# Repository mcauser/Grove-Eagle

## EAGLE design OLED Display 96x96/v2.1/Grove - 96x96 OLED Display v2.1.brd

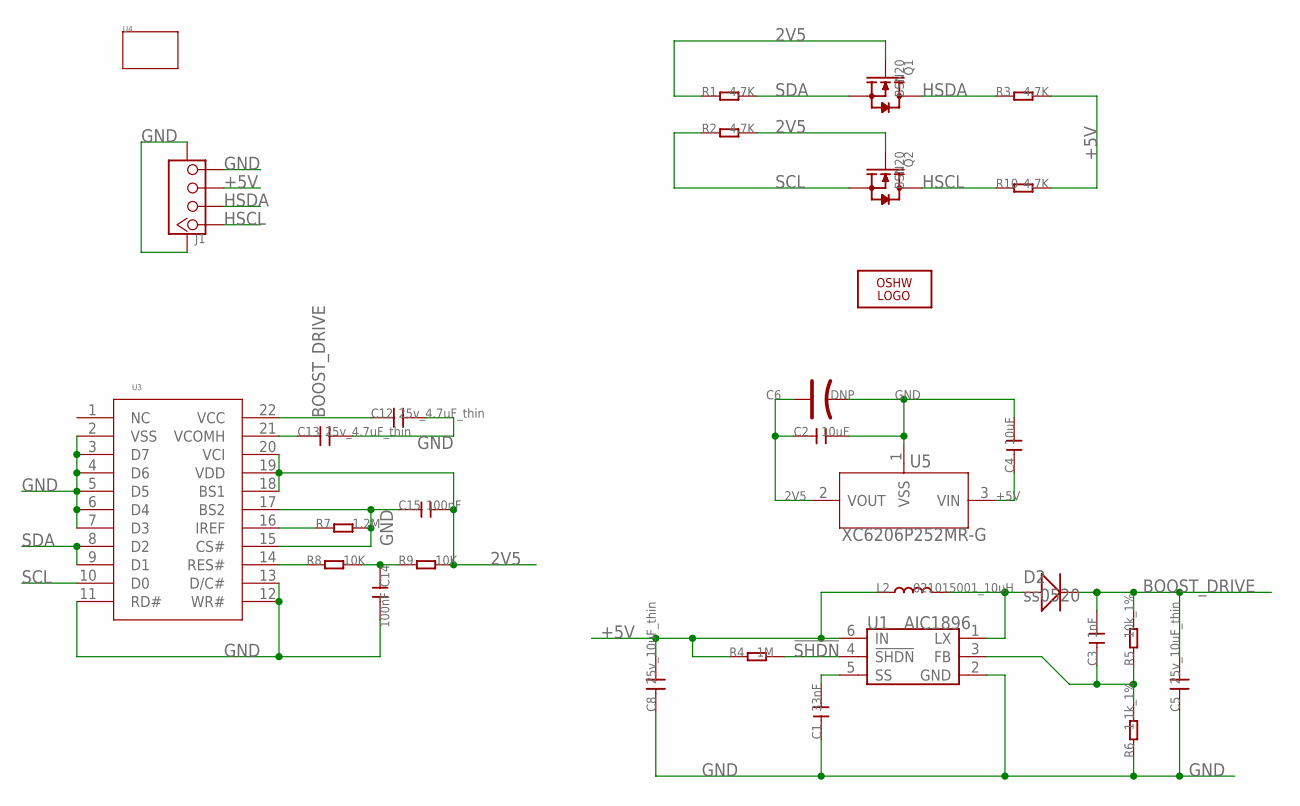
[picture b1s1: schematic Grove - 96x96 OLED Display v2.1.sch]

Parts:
C1: 33nF; C0603
C2, C4: 10uF; C0805
C3: 1nF; C0603
C5, C8: 25v_10uF_thin; 0805
C6: DNP; AVX-A
C12, C13: 25v_4.7uF_thin; 0805
C14, C15: 100nF; C0603
D2: ss0520; SOD123
J1: TWIG-4P-2.0-SMD-FEMALE-REINFORCE'90D'; 4P-SMD-2.0-90D
L2: 021015001_10uH; 0806
LOGO2: LOGO-OSHW-FILLX0200-NT; OSHW_FILLX200_NOTEXT
Q1, Q2: BSN20; SOT23
R1, R2, R3, R10: 4.7K; R0603
R4: 1M; R0603
R5: 10k_1%; R0603
R6: 1.1k_1%; R0603
R7: 1.2M; 0603
R8, R9: 10K; 0603
U1: AIC1896; SOT23-6
U3: LY120-096096
U4: TWIG-2X2U; 2X2U-DIM-W/-DRILL
U5: XC6206P252MR-G; SOT23

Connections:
2V5: C2.1, C6.+, C15.2, Q1.1 (G), Q2.1 (G), R1.1, R2.2, R9.2, U3.18 (BS1), U3.19 (VDD), U3.20 (VCI), U5.2 (VOUT)
!SHDN: R4.2, U1.4 (!SHDN)
+5V: C4.1, C8.2, J1.3, L2.1, R3.2, R4.1, R10.2, U1.6 (IN), U5.3 (VIN)
BOOST_DRIVE: C3.2, C5.2, C12.1, D2.-, R5.2, U3.22 (VCC)
GND: C1.1, C2.2, C4.2, C5.1, C6.-, C8.1, C12.2, C13.2, C14.2, C15.1, J1.4, J1.SS1, J1.SS2, R6.1, R7.2, U1.2 (GND), U3.2 (VSS), U3.3 (D7), U3.4 (D6), U3.5 (D5), U3.6 (D4), U3.7 (D3), U3.11 (RD#), U3.12 (WR#), U3.13 (D/C#), U3.15 (CS#), U3.17 (BS2), U5.1 (VSS)
HSCL: J1.1, Q2.3 (D), R10.1
HSDA: J1.2, Q1.3 (D), R3.1
unnamed: D2.+, L2.2, U1.1 (LX)
unnamed: C1.2, U1.5 (SS)
unnamed: C3.1, R5.1, R6.2, U1.3 (FB)
unnamed: C13.1, U3.21 (VCOMH)
unnamed: R7.1, U3.16 (IREF)
unnamed: R8.1, U3.14 (RES#)
unnamed: C14.1, R8.2, R9.1
SCL: Q2.2 (S), R2.1, U3.10 (D0)
SDA: Q1.2 (S), R1.2, U3.8 (D2), U3.9 (D1)

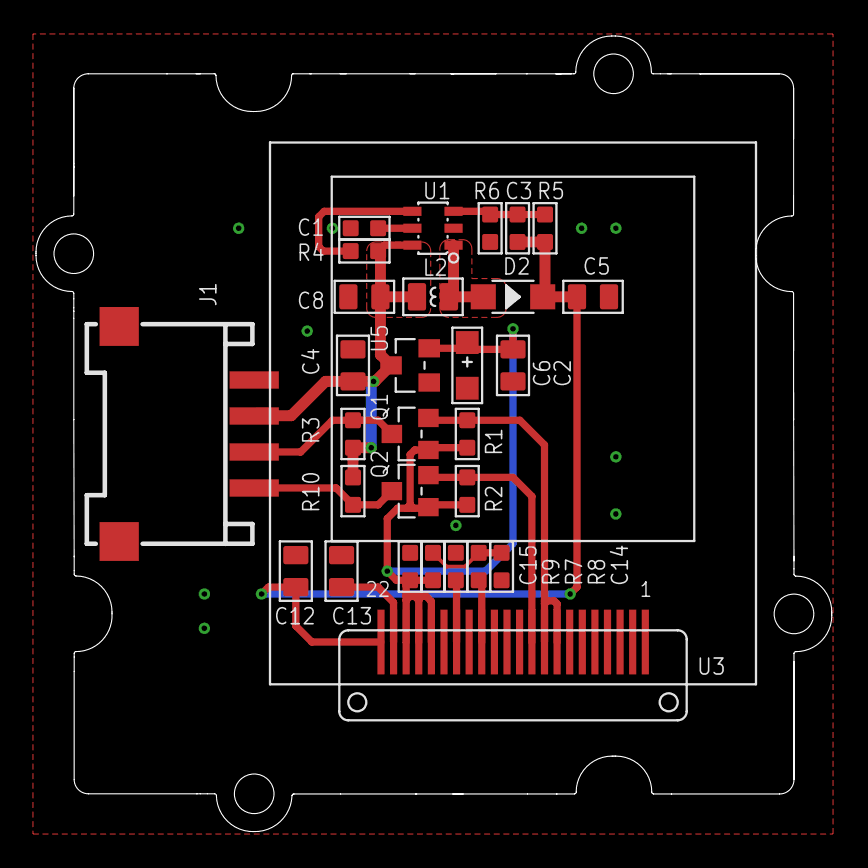
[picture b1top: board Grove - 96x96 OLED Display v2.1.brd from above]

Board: 2 copper layers, 44.2 x 44.2 mm, 32 parts (2 on the bottom side), 16 nets.

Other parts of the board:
U$1: TWIGLOGO

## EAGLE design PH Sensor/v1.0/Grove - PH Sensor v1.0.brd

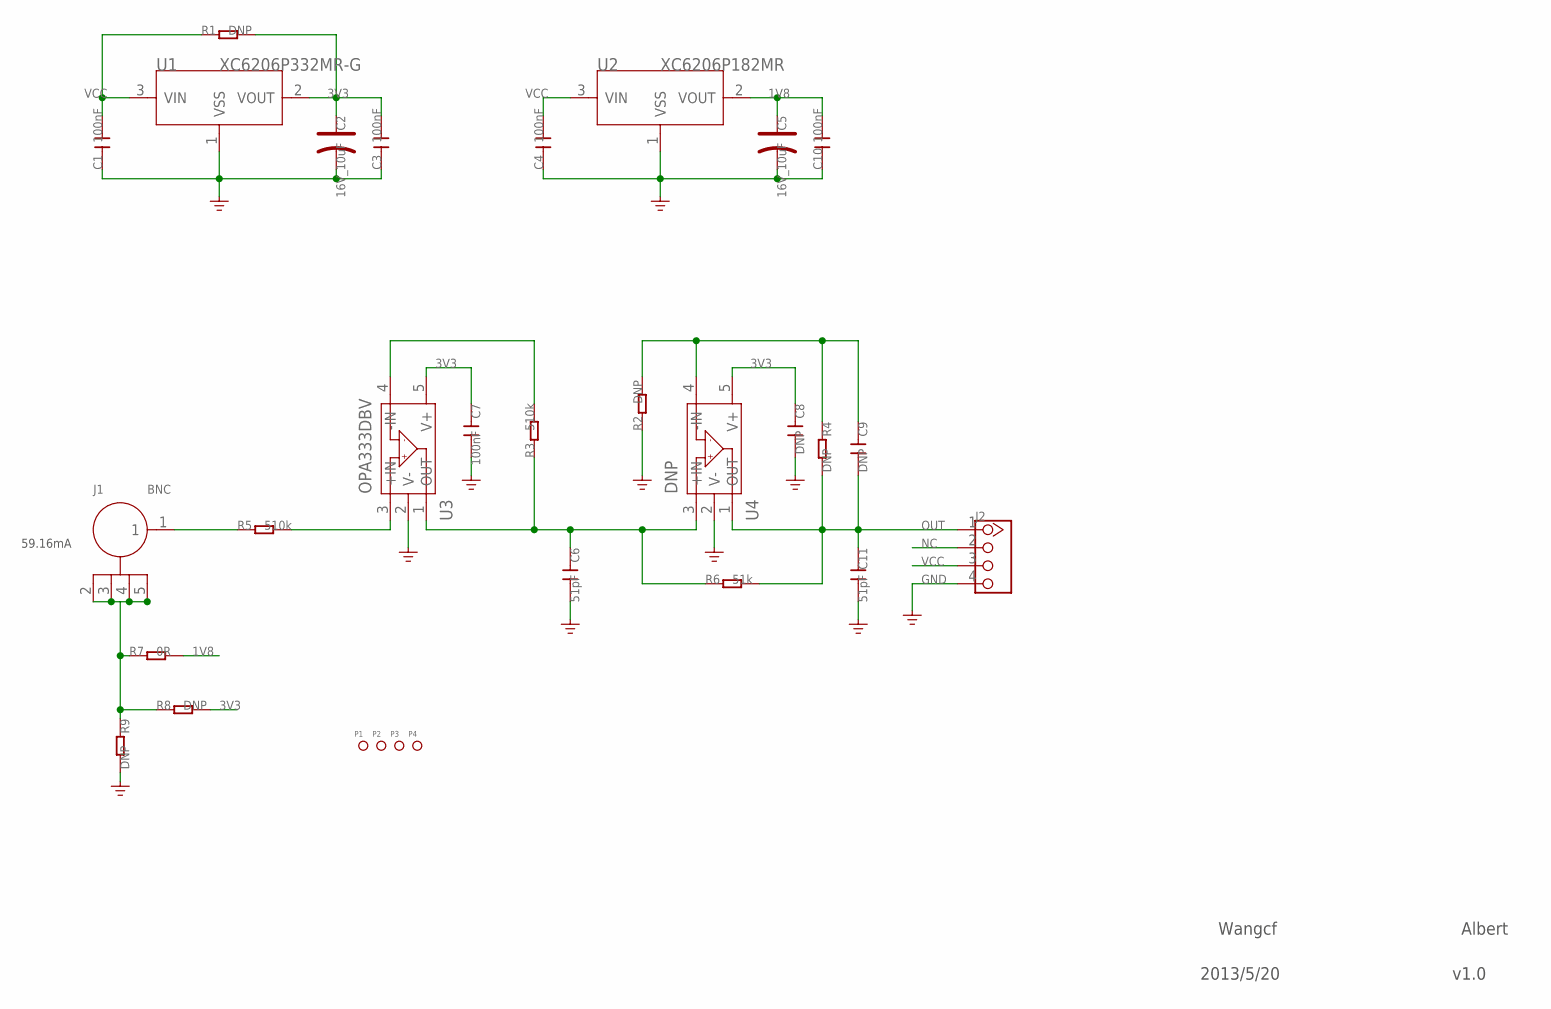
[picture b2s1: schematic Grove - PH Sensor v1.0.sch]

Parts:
C1, C3, C4, C7, C10: 100nF; C0603
C2, C5: 16V_10uF; AVX-A
C6, C11: 51pF; C0603
C8, C9: DNP; C0603
J1: BNC; 2P-10X10X12H-90D
J2: TWIG-4P-2.0-2.0; 4P-2.0
P1, P2, P3, P4: PAD-MARK; ROUND-MARK-1.0
R1, R2, R4, R8, R9: DNP; R0603
R3, R5: 510k; R0603
R6: 51k; R0603
R7: 0R; R0603
U1: XC6206P332MR-G; SOT23
U2: XC6206P182MR; SOT23
U3: OPA333DBV; SOT23-5
U4: DNP; SOT23-5

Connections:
1V8: C5.+, C10.2, R7.2, U2.2 (VOUT)
3V3: C2.+, C3.2, C7.1, C8.1, R1.2, R8.2, U1.2 (VOUT), U3.5 (V+), U4.5 (V+)
GND: C1.1, C2.-, C3.1, C4.1, C5.-, C6.2, C7.2, C8.2, C10.1, C11.2, J2.4, R2.1, R9.2, U1.1 (VSS), U2.1 (VSS), U3.2 (V-), U4.2 (V-)
unnamed: J1.1, R5.1
unnamed: R5.2, U3.3 (+IN)
unnamed: C6.1, R3.1, R6.1, U3.1 (OUT), U4.3 (+IN)
unnamed: R3.2, U3.4 (-IN)
unnamed: C9.1, R2.2, R4.1, U4.4 (-IN)
unnamed: J1.2, J1.3, J1.4, J1.5, R7.1, R8.1, R9.1
NC: J2.2
OUT: C9.2, C11.1, J2.1, R4.2, R6.2, U4.1 (OUT)
VCC: C1.2, C4.2, J2.3, R1.1, U1.3 (VIN), U2.3 (VIN)

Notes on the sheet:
59.16mA
Wangcf
Albert
2013/5/20
v1.0

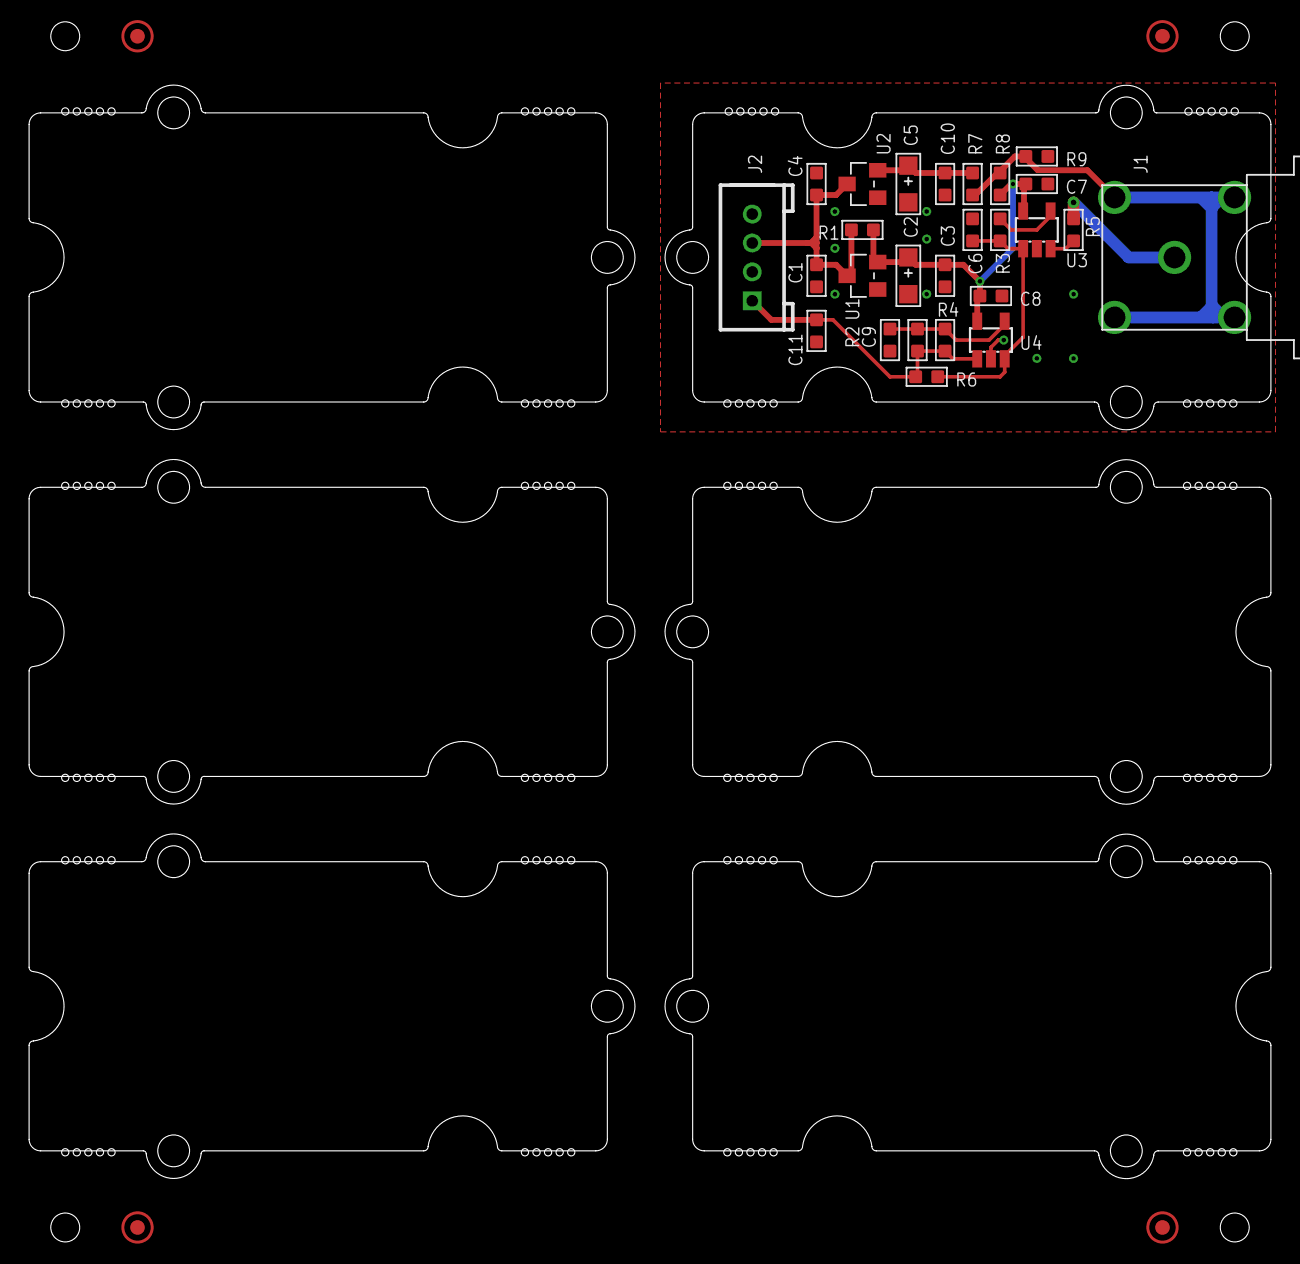
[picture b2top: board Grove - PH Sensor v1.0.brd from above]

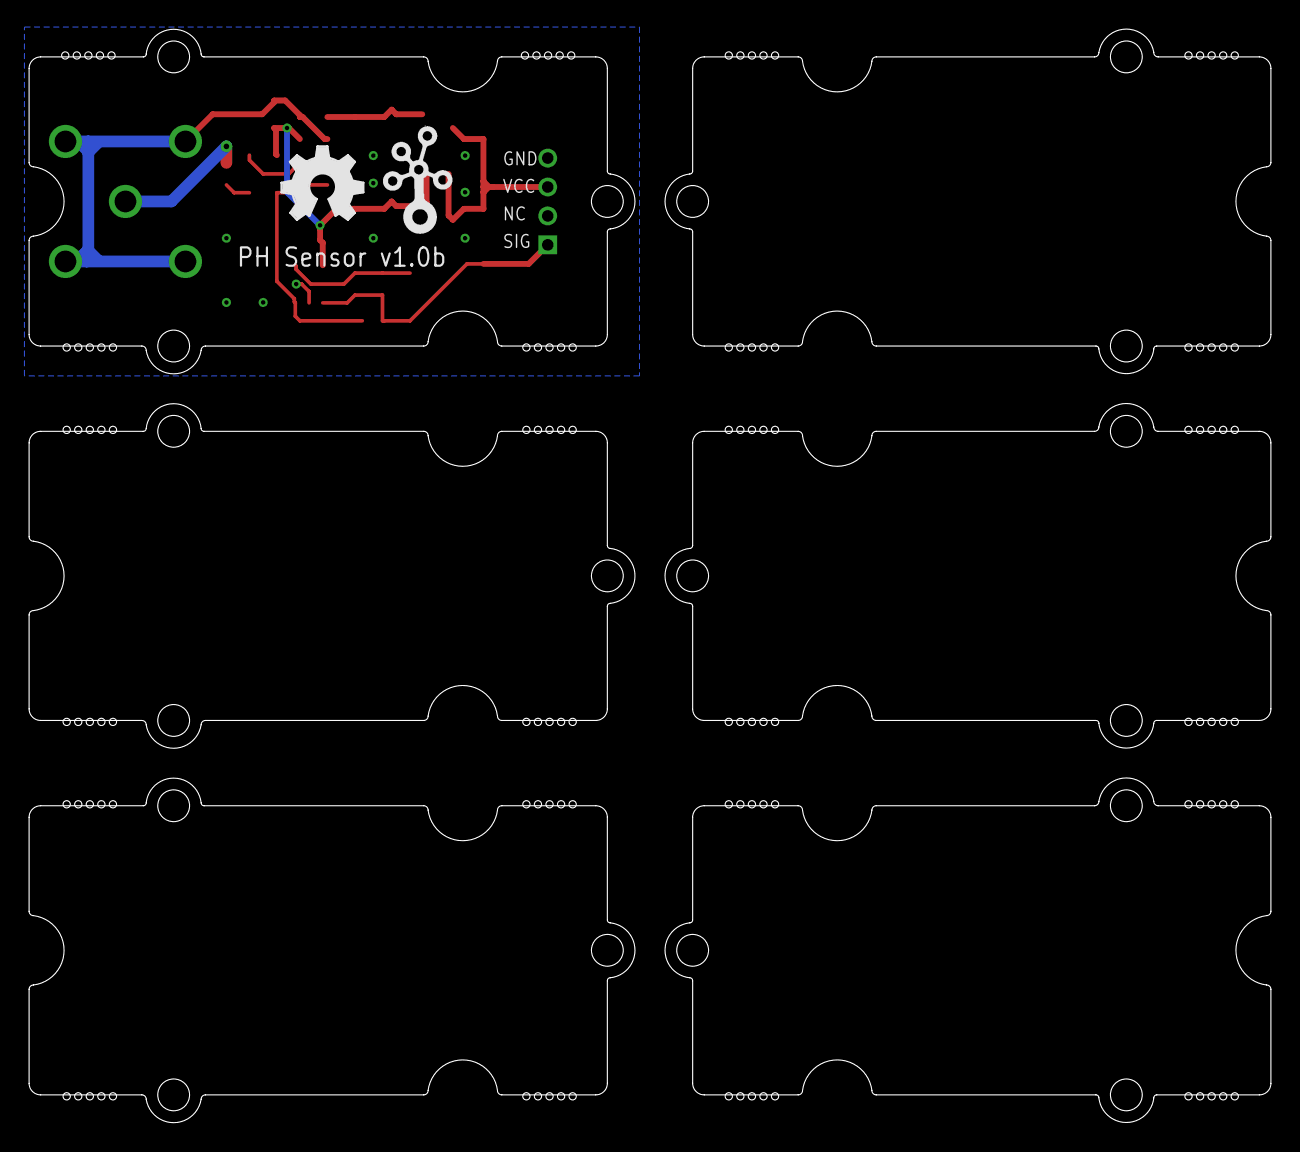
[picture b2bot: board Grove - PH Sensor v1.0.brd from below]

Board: 2 copper layers, 85.9 x 75.6 mm, 38 parts (2 on the bottom side), 11 nets.

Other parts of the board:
U$12, U$16, U$17, U$18, U$19, U$20: 2U-DIM-W/DRILL
U$13: OSHW_FILLX200_NOTEXT
U$14: TWIGLOGO

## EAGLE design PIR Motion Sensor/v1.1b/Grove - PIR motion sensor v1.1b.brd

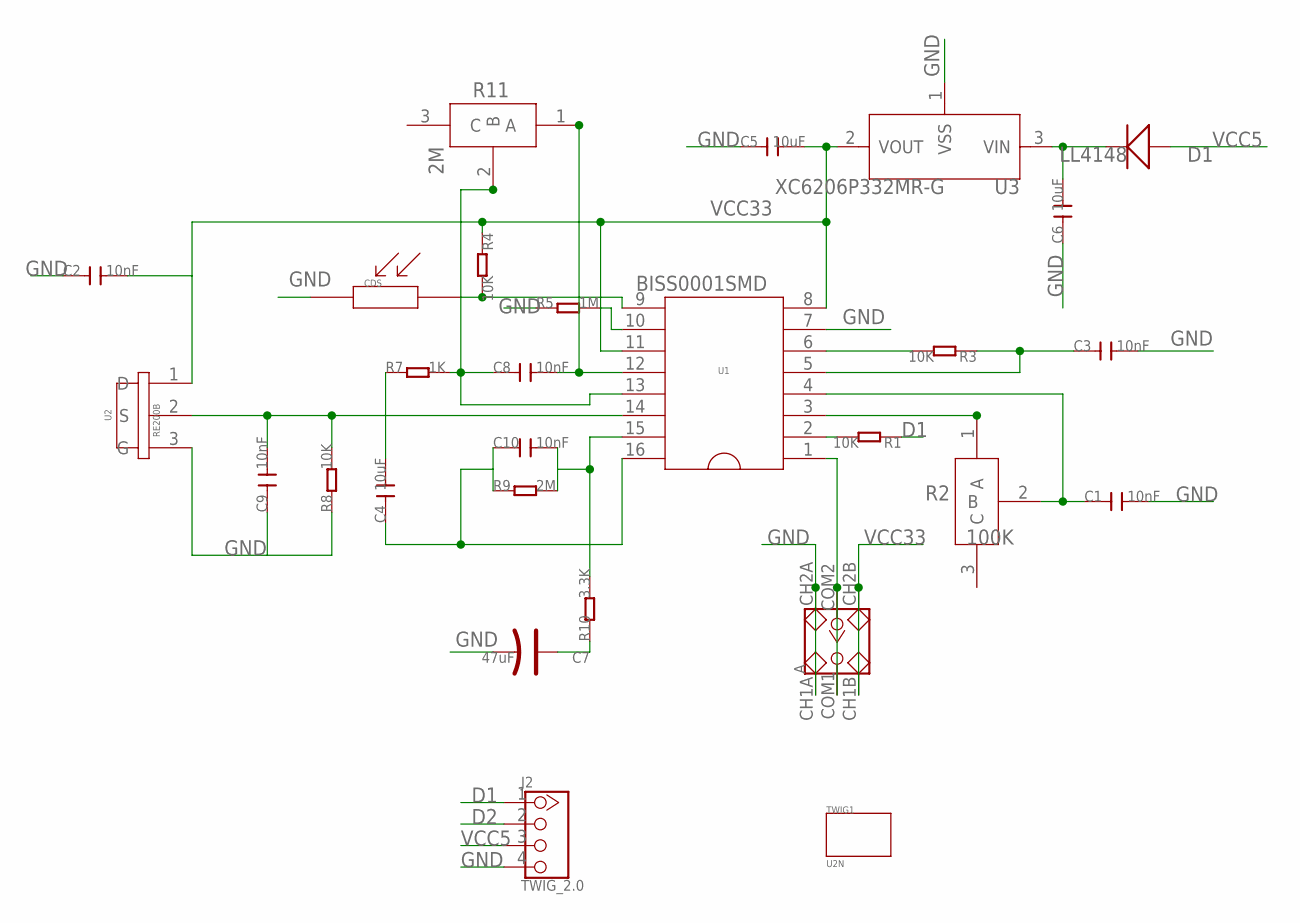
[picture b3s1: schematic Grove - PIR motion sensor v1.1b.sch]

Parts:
A: SWITCH-2CH-6P; 6P-2CH-2.54-7.6X3.0
C1, C2, C3, C8, C9, C10: 10nF; C0603
C4, C5, C6: 10uF; C0805
C7: 47uF; AVX-B
CDS: CDS
D1: LL4148; SOD123
J2: TWIG_2.0; 2.0_1X4
R1, R3, R4, R8: 10K; R0603
R2: 100K; R_REG
R5: 1M; R0603
R7: 1K; R0603
R9: 2M; R0603
R10: 3.3K; R0603
R11: 2M; R_REG
TWIG1: U2N
U1: BISS0001SMD; SOP16
U2: RE200B
U3: XC6206P332MR-G; SOT23

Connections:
D1: J2.1, R1.1
D2: J2.2
GND: A.CH1A, A.CH2A, C1.2, C2.1, C3.2, C5.1, C6.1, C7.-, C9.1, CDS.1, J2.4, R5.1, R8.1, U1.7, U2.3 (G), U3.1 (VSS)
unnamed: R2.1 (A), U1.3
unnamed: C1.1, R2.2 (B), U1.4
unnamed: C6.2, D1.-, U3.3 (VIN)
unnamed: A.COM1, A.COM2, U1.1
unnamed: R1.2, U1.2
unnamed: R3.2, U1.6
unnamed: C3.1, R3.1, U1.5
unnamed: CDS.2, R4.2, U1.9
unnamed: R5.2, U1.10
unnamed: C9.2, R8.2, U1.14, U2.2 (S)
unnamed: C8.2, R11.1 (A), U1.12
unnamed: C8.1, R7.2, R11.2 (B), U1.13
unnamed: C4.1, C10.1, R9.1, U1.16
unnamed: C10.2, R9.2, R10.2, U1.15
unnamed: C4.2, R7.1
unnamed: C7.+, R10.1
VCC5: D1.+, J2.3
VCC33: A.CH1B, A.CH2B, C2.2, C5.2, R4.1, U1.8, U1.11, U2.1 (D), U3.2 (VOUT)

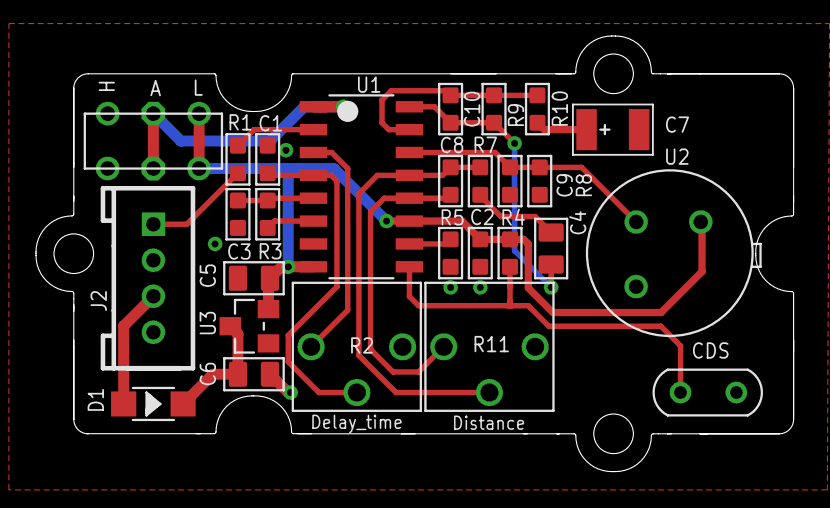
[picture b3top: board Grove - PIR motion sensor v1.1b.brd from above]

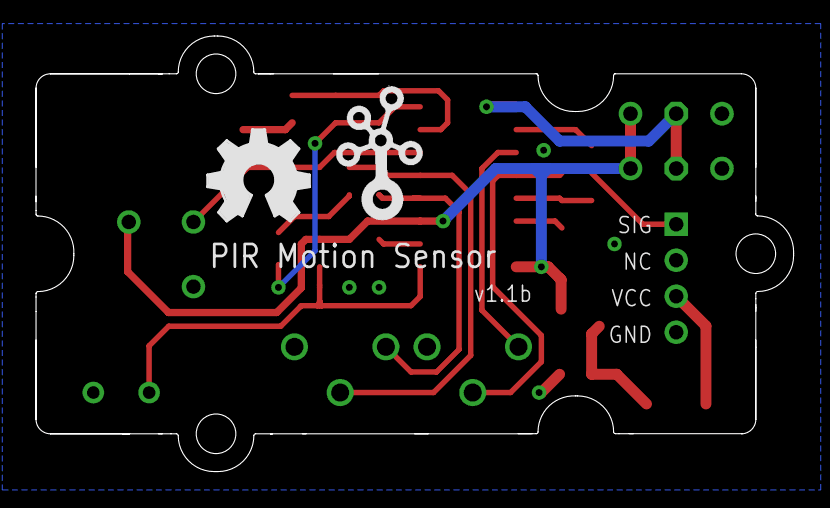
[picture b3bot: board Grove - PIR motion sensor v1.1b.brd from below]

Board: 2 copper layers, 42.1 x 24.2 mm, 30 parts (2 on the bottom side), 20 nets.

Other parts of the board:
U$3: OSHW_FILLX200_NOTEXT
U$4: TWIGLOGO

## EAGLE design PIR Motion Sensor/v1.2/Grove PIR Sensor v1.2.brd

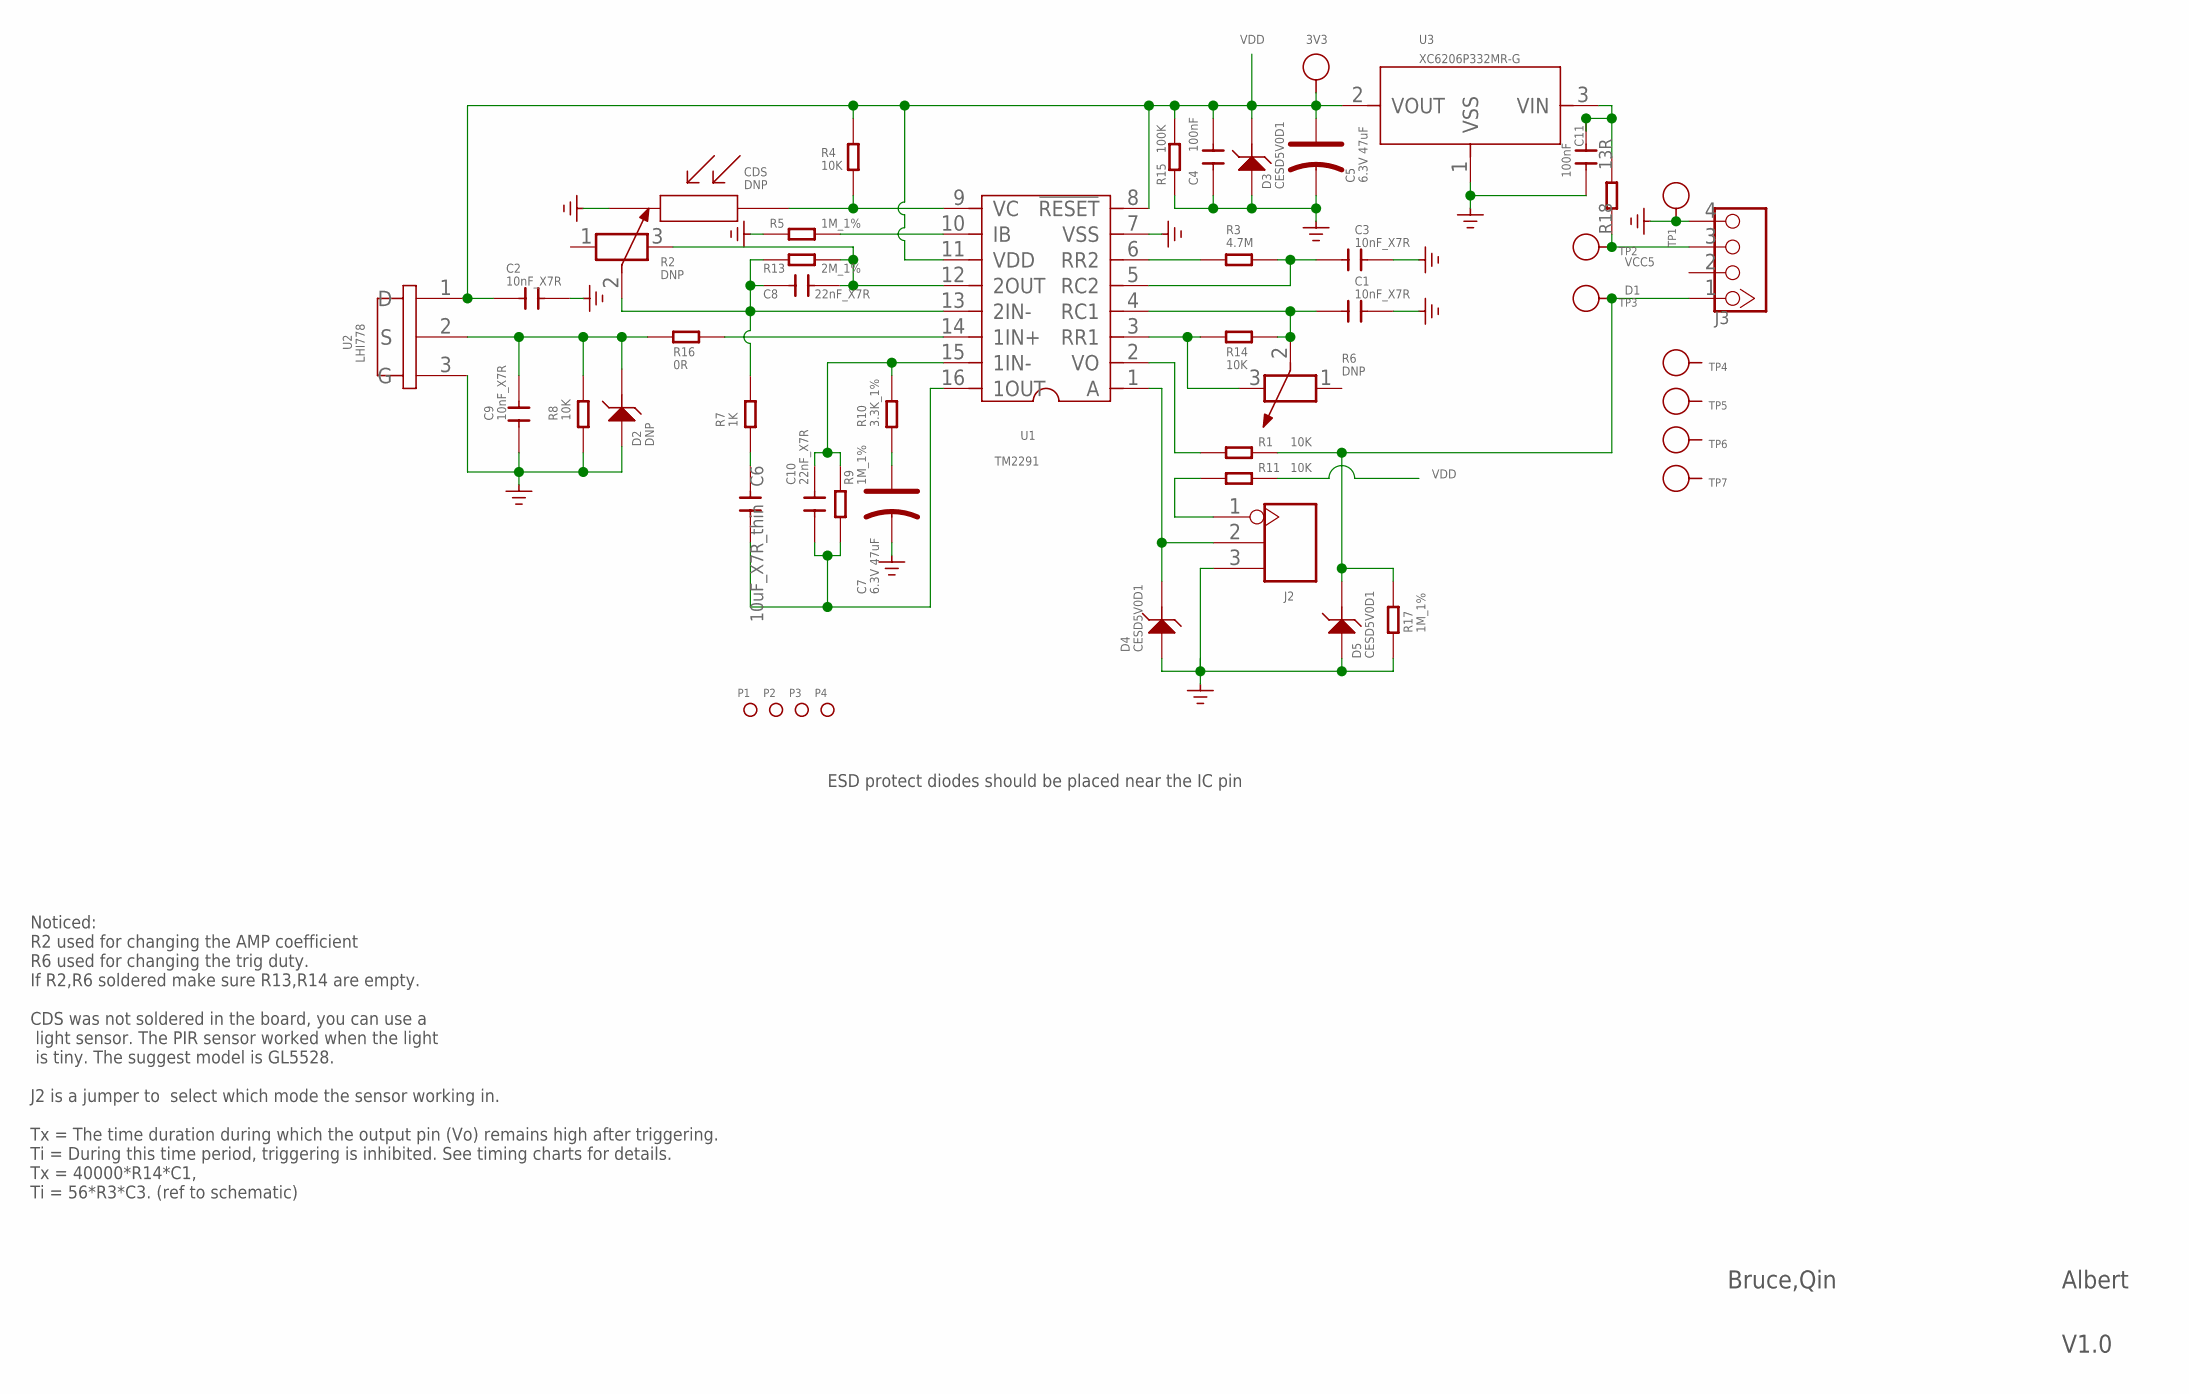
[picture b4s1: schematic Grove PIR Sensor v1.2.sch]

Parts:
3V3: PAD-TEST-POINT'3535'; TP_3535
C1, C2, C3, C9: 10nF_X7R; C0603
C4, C11: 100nF; C0603
C5, C7: 6.3V 47uF; AVX-A
C6: 10uF_X7R_thin; C0805
C8, C10: 22nF_X7R; C0603
CDS: DNP; CDS
D2: DNP; SOD123-2.7X1.6
D3, D4, D5: CESD5V0D1; SOD123-2.7X1.6
J2: HEADER-3P-2.54; 3P-2.54
J3: TWIG-4P-2.0-2.0; 4P-2.0
P1, P2, P3, P4: PAD-MARK; ROUND-MARK-1.0
R1, R4, R8, R11, R14: 10K; R0603
R2, R6: DNP; 3P-SMD-SQUA-3.6X3.3
R3: 4.7M; R0603
R5, R9, R17: 1M_1%; R0603
R7: 1K; R0603
R10: 3.3K_1%; R0603
R13: 2M_1%; R0603
R15: 100K; R0603
R16: 0R; R0603
R18: 13R; R1206
TP1, TP2, TP3, TP4, TP5, TP6, TP7: PAD-TEST-POINT'3535'; TP_3535
U1: TM2291; SOP16
U2: LHI778; 3P-D8.1MM
U3: XC6206P332MR-G; SOT23

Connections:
D1: D5.2, J3.1, R1.1, R17.2, TP3.T
GND: C1.2, C2.1, C3.2, C4.2, C5.-, C7.-, C9.1, C11.1, CDS.1, D2.1, D3.1, D4.1, D5.1, J2.3, J3.4, R5.1, R8.1, R15.2, R17.1, TP1.T, U1.7 (VSS), U2.3 (G), U3.1 (VSS)
unnamed: R6.3 (2), R14.1, U1.3 (RR1)
unnamed: C1.1, R6.2 (3), R14.2, U1.4 (RC1)
unnamed: J2.1, R11.2
unnamed: R1.2, U1.2 (VO)
unnamed: R3.2, U1.6 (RR2)
unnamed: C3.1, R3.1, U1.5 (RC2)
unnamed: CDS.2, R4.2, U1.9 (VC)
unnamed: R5.2, U1.10 (IB)
unnamed: C9.2, D2.2, R8.2, R16.2, U2.2 (S)
unnamed: C8.2, R2.3 (2), R13.1, U1.12 (2OUT)
unnamed: C8.1, R2.2 (3), R7.2, R13.2, U1.13 (2IN-)
unnamed: C6.2, C10.1, R9.1, U1.16 (1OUT)
unnamed: C10.2, R9.2, R10.2, U1.15 (1IN-)
unnamed: C6.1, R7.1
unnamed: D4.2, J2.2, U1.1 (A)
unnamed: C7.+, R10.1
unnamed: R16.1, U1.14 (1IN+)
unnamed: C11.2, R18.2, U3.3 (VIN)
VCC5: J3.3, R18.1, TP2.T
VDD: 3V3.T, C2.2, C4.1, C5.+, D3.2, R4.1, R11.1, R15.1, U1.8 (!RESET), U1.11 (VDD), U2.1 (D), U3.2 (VOUT)

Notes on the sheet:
Noticed: R2 used for changing the AMP coefficient R6 used for changing the trig duty. If R2,R6 soldered make sure R13,R14 are empty. CDS was not soldered in the board, you can use a light sensor. The PIR sensor worked when the light is tiny. The suggest model is GL5528. J2 is a jumper to select whi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
ESD protect diodes should be placed near the IC pin
Bruce,Qin
Albert
V1.0

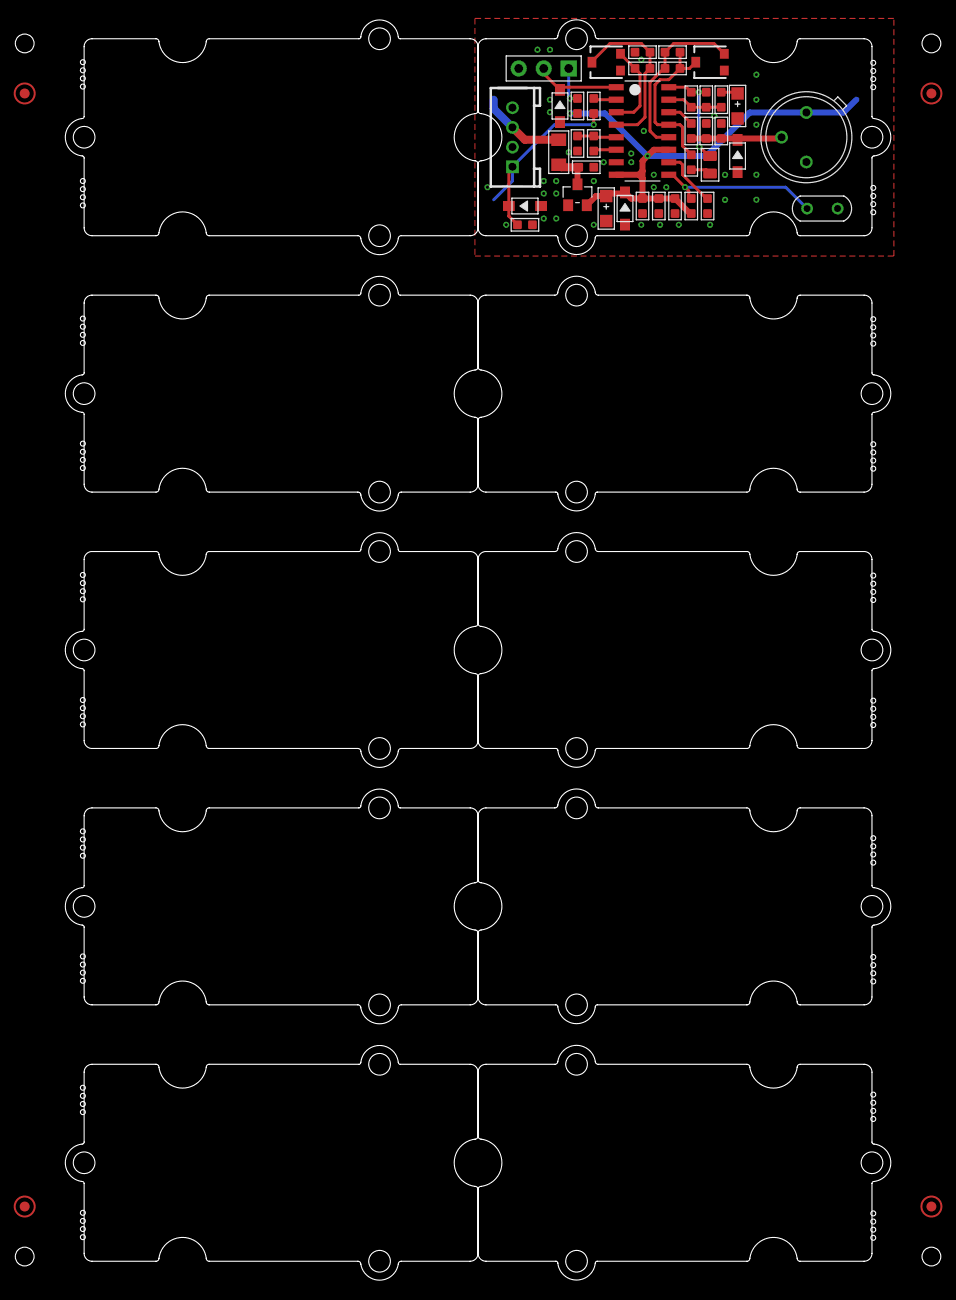
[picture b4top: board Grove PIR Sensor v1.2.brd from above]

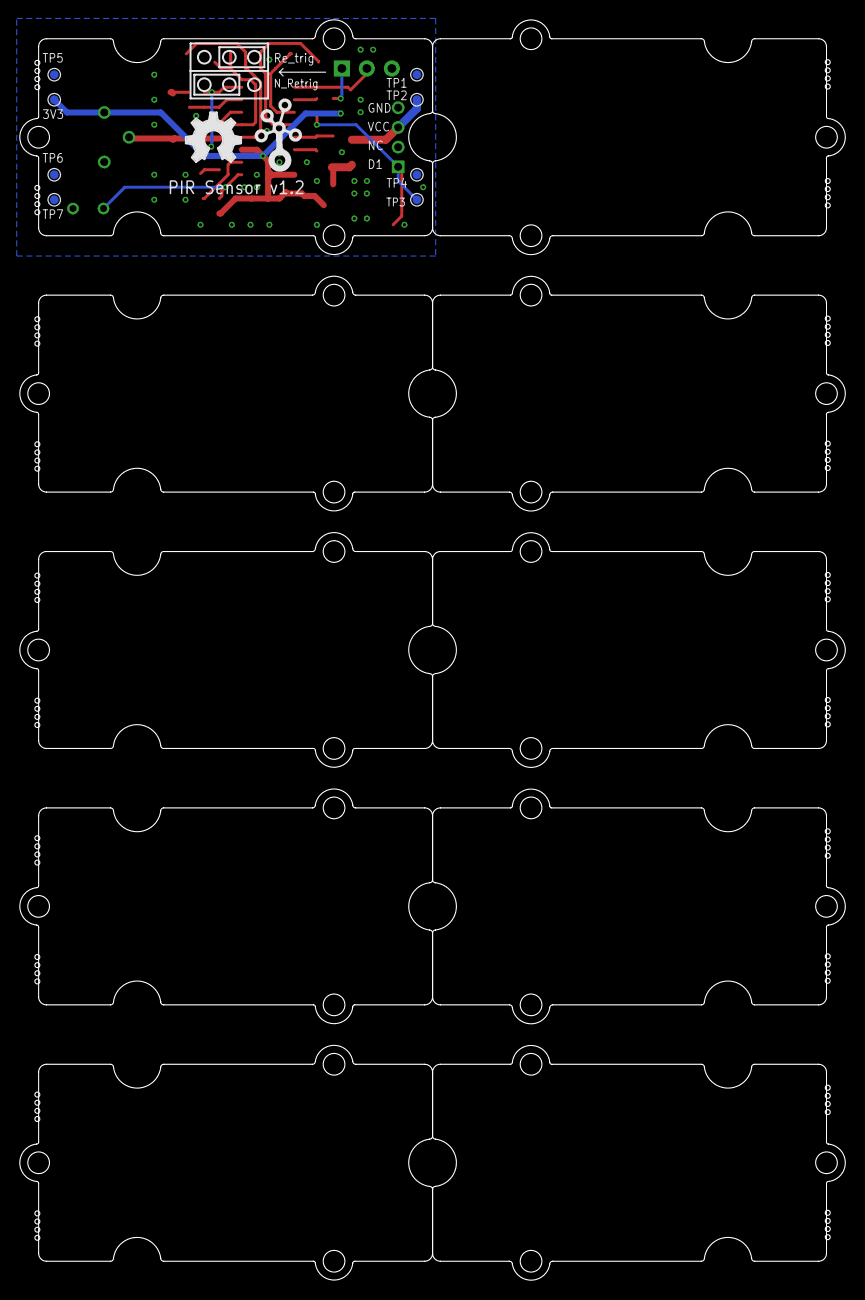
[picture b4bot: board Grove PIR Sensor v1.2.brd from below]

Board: 2 copper layers, 83.8 x 128.0 mm, 62 parts (10 on the bottom side), 22 nets.

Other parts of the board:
U$3, U$17, U$18, U$19, U$20, U$21, U$22, U$23, U$24, U$25: GROVE-2CONNECTOR
U$16: OSHW_FILLX200_NOTEXT
U$26: TWIGLOGO

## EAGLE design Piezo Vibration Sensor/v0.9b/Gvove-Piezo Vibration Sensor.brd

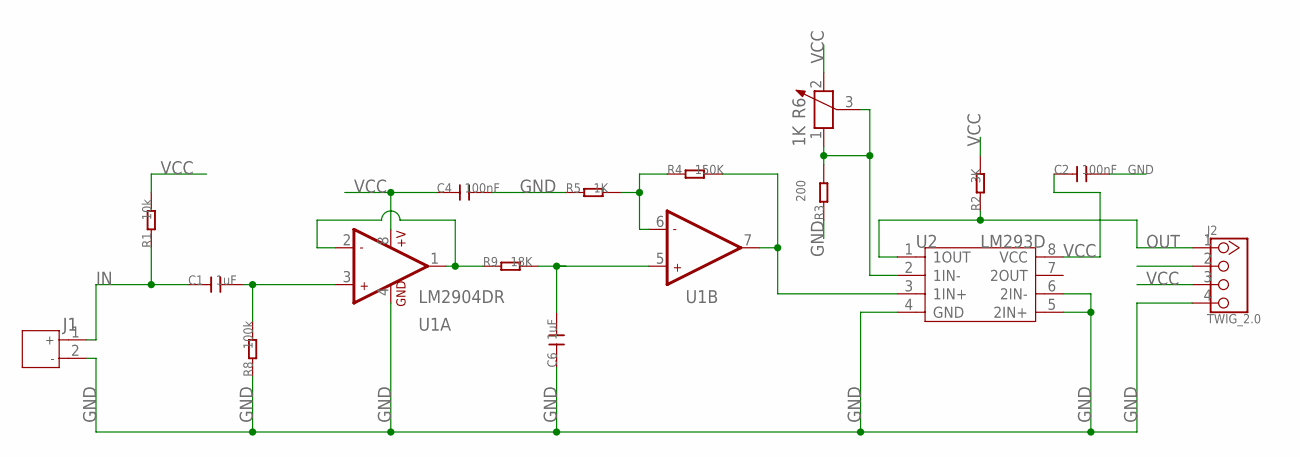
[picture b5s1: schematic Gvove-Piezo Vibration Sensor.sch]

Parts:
C1, C6: 1uF; C0603
C2, C4: 100nF; C0603
J1: JACK-JST-2P-PW'2.0'; JST-2.0
J2: TWIG_2.0; 2.0_1X4
R1: 10k; R0603
R2: 3K; R0603
R3: 200; R0603
R4: 150K; R0603
R5: 1K; R0603
R6: 1K; 3P-SQUA-7X6.8
R8: 100k; R0603
R9: 18K; R0603
U1: LM2904DR; SO08
U2: LM293D; SOIC8-6.0

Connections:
GND: C2.2, C4.2, C6.1, J1.2, J2.4, R3.1, R5.1, R8.1, U1.4 (GND), U2.4 (GND), U2.5 (2IN+), U2.6 (2IN-)
IN: C1.1, J1.1, R1.1
unnamed: R3.2, R6.1, R6.3, U2.2 (1IN-)
unnamed: C1.2, R8.2, U1.3 (+IN1)
unnamed: R9.1, U1.1 (OUT1), U1.2 (-IN1)
unnamed: R4.1, R5.2, U1.6 (-IN2)
unnamed: R4.2, U1.7 (OUT2), U2.3 (1IN+)
unnamed: C6.2, R9.2, U1.5 (+IN2)
OUT: J2.1, R2.1, U2.1 (1OUT)
VCC: C2.1, C4.1, J2.3, R1.2, R2.2, R6.2, U1.8 (+V), U2.8 (VCC)

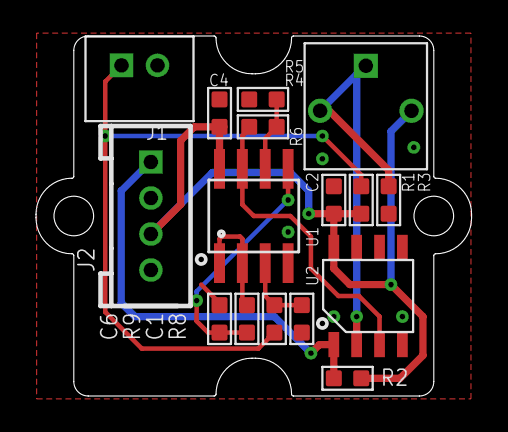
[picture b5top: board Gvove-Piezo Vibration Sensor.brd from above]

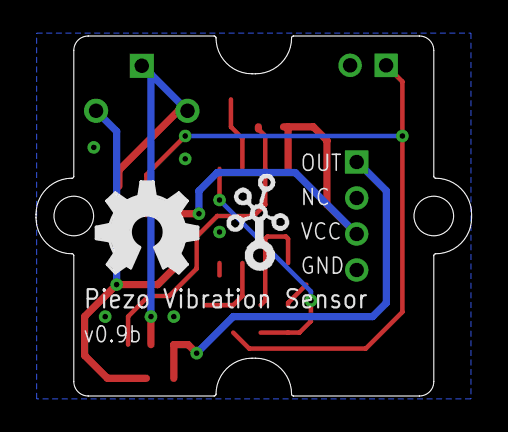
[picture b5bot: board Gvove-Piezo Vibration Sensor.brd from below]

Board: 2 copper layers, 24.2 x 20.0 mm, 19 parts (2 on the bottom side), 10 nets.

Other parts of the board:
U$1: 1U-DIM-W/-DRILL
U$3: TWIGLOGO_SMALL
U$4: OSHW_FILLX200_NOTEXT
